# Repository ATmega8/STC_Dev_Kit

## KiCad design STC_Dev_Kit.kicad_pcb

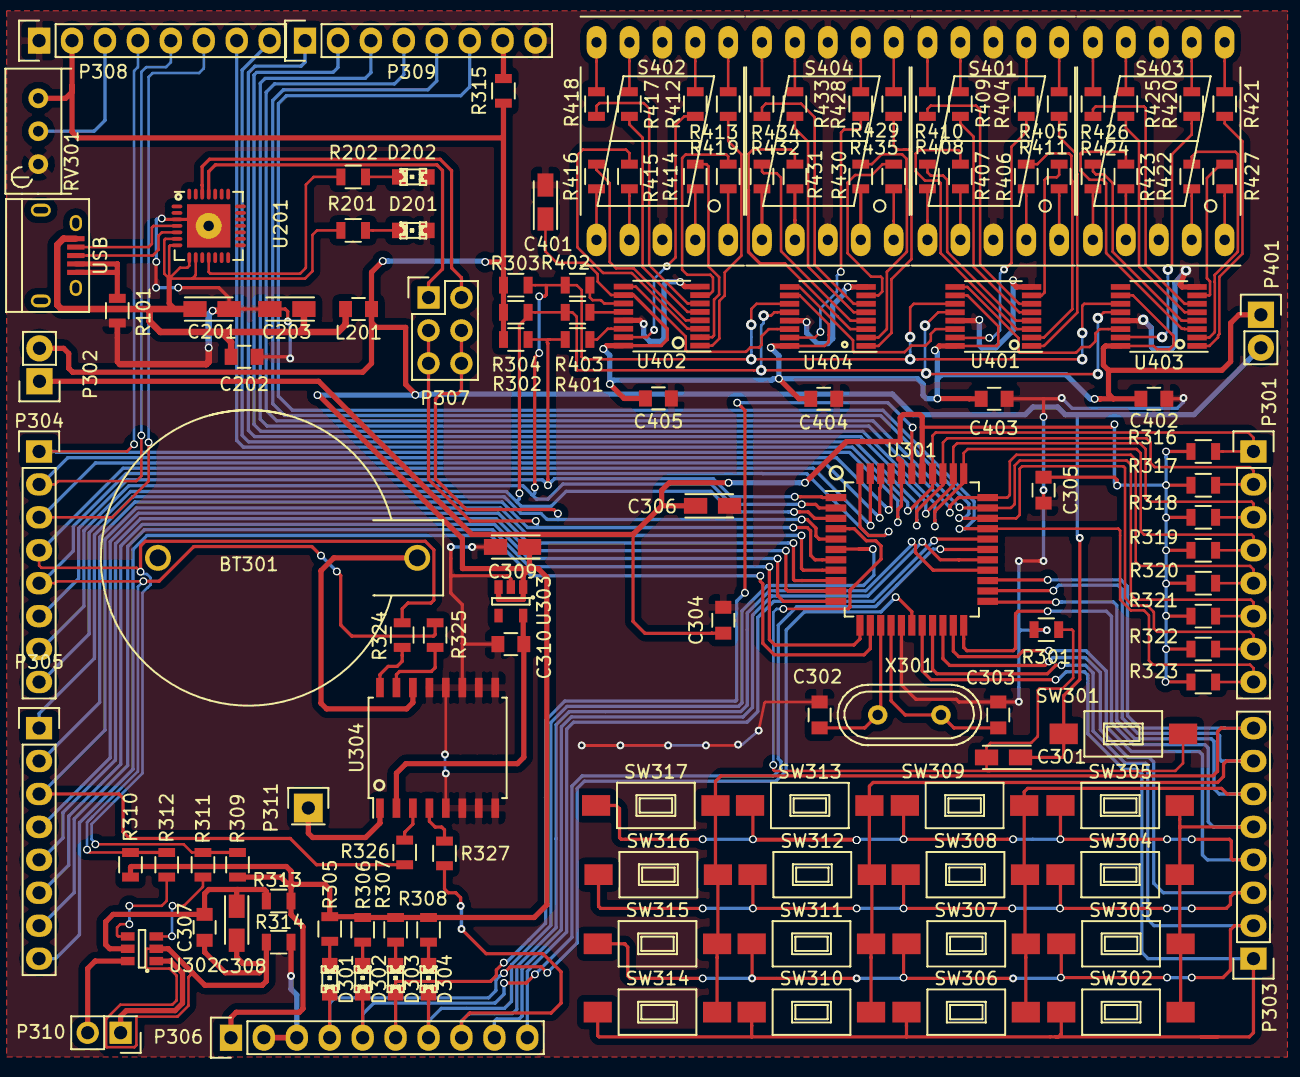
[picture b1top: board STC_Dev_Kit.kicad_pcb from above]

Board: 2 copper layers, 136 parts (0 on the bottom side), 144 nets.

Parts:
BT301: CR2032
C201: 4.7u; TantalC_SizeA_EIA-3216_Reflow
C202, C304, C305, C307, C310, C402, C403, C404, C405: 0.1u; C_0805
C203, C301, C306, C308, C309, C401: 10u; TantalC_SizeA_EIA-3216_Reflow
C302, C303: 22p; C_0805
D201: LED_PWR; LED-0805
D202: LED_STATUS; LED-0805
D301, D302, D303, D304: LED; LED-0805
L201: INDUCTOR_SMALL; C_0805
P301: P0; Pin_Header_Straight_1x08
P302: P1; Pin_Header_Straight_1x08
P303: P2; Pin_Header_Straight_1x08
P304: MCU POWER; Pin_Header_Straight_1x02
P305: P3; Pin_Header_Straight_1x08
P306: P4; Pin_Header_Straight_1x10
P307: USART SWITCH; Pin_Header_Straight_2x03
P308: LCD1602; Pin_Header_Straight_1x08
P309: CONN_8; Pin_Header_Straight_1x08
P310: Analog Input; Pin_Header_Straight_2x01
P311: 32KHz Out; Pin_Header_Straight_1x01
P401: LED POWER; Pin_Header_Straight_1x02
R101, R311, R312, R313, R314, R324, R325, R401, R402, R403: 0; R_0805
R201, R202, R302, R303, R304, R309, R310, R316, R317, R318, R319, R320, R321, R322, R323: 4.7k; R_0805
R301: 10k; R_0805
R305, R306, R307, R308, R326, R327: 1k; R_0805
R315: 10; R_0805
R404, R405, R406, R407, R408, R409, R410, R411, R412, R413, R414, R415, R416, R417, R418, R419, R420, R421, R422, R423, R424, R425, R426, R427, R428, R429, R430, R431, R432, R433, R434, R435: 470; R_0805
RV301: 10k; Potentiometer_Bourns_3296W_3-8Zoll_Inline_ScrewUp
S401, S402, S403, S404: 7SEGM; 7SegmentLED_LTS6760_LTS6780
SW301: RESET; SW_SPST_FSMSM
SW302, SW303, SW304, SW305, SW306, SW307, SW308, SW309, SW310, SW311, SW312, SW313, SW314, SW315, SW316, SW317: SW_PUSH_SMALL; SW_SPST_FSMSM
U201: CP2102; QFN-28-1EP_5x5mm_Pitch0.5mm
U301: STC89C52RC; LQFP-44_10x10mm_Pitch0.8mm
U302: MCP3421; SOT-23-6
U303: TPS76933; SOT-23-5
U304: DS3231; SOIC-16_7.5x10.3mm_Pitch1.27mm
U401, U402, U403, U404: 74HC595; TSSOP-16_4.4x5mm_Pitch0.65mm
USB: USB_CONN; USB_Micro-B
X301: CRYSTAL; Crystal_HC49-U_Vertical

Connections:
+5V: C301.1, C309.1, L201.2, P304.2, P306.1, P308.2, P401.2, R302.2, R303.2, R304.2, R305.1, R306.1, R307.1, R308.1, R309.2, R310.2, R313.2, R315.2, RV301.3, SW301.2, U303.1, U303.3
/LED_Display/DS: P302.6, R302.1, R401.2, U301.1
/LED_Display/DSO1: U402.9, U404.14
/LED_Display/DSO2: U401.14, U404.9
/LED_Display/DSO3: U401.9, U403.14
/STC_CORE/ADC_VDD: C307.1, C308.1, R313.1, U302.5
/STC_CORE/ADC_VSS: C307.2, C308.2, R314.1, U302.2
/STC_CORE/LED_RCK: P302.8, R304.1, R403.2, U301.3, U401.12, U403.12, U404.12
/STC_CORE/LED_SCK: P302.7, R303.1, R402.2, U301.2, U401.11, U403.11, U404.11
/STC_CORE/MCU_VDD: C304.1, C305.1, C306.1, P304.1, R316.1, R317.1, R318.1, R319.1, R320.1, R321.1, R322.1, R323.1, U301.38
/STC_CORE/P0.0: P301.1, P308.7, R316.2, U301.37
/STC_CORE/P0.1: P301.2, P308.8, R317.2, U301.36
/STC_CORE/P0.2: P301.3, P309.1, R318.2, U301.35
/STC_CORE/P0.3: P301.4, P309.2, R319.2, U301.34
/STC_CORE/P0.4: P301.5, P309.3, R320.2, U301.33
/STC_CORE/P0.5: P301.6, P309.4, R321.2, U301.32
/STC_CORE/P0.6: P301.7, P309.5, R322.2, U301.31
/STC_CORE/P0.7: P301.8, P309.6, R323.2, U301.30
/STC_CORE/P1.0: P302.1, P308.4, U301.40
/STC_CORE/P1.1: P302.2, P308.5, U301.41
/STC_CORE/P1.2: P302.3, P308.6, U301.42
/STC_CORE/P1.3: P302.4, R309.1, R311.2, R324.1, U301.43
/STC_CORE/P1.4: P302.5, R310.1, R312.2, R325.1, U301.44
/STC_CORE/P2.0: P303.1, SW302.1, SW306.1, SW310.1, SW314.1, U301.18
/STC_CORE/P2.1: P303.2, SW303.1, SW307.1, SW311.1, SW315.1, U301.19
/STC_CORE/P2.2: P303.3, SW304.1, SW308.1, SW312.1, SW316.1, U301.20
/STC_CORE/P2.3: P303.4, SW305.1, SW309.1, SW313.1, SW317.1, U301.21
/STC_CORE/P2.4: P303.5, SW302.2, SW303.2, SW304.2, SW305.2, U301.22
/STC_CORE/P2.5: P303.6, SW306.2, SW307.2, SW308.2, SW309.2, U301.23
/STC_CORE/P2.6: P303.7, SW310.2, SW311.2, SW312.2, SW313.2, U301.24
/STC_CORE/P2.7: P303.8, SW314.2, SW315.2, SW316.2, SW317.2, U301.25
/STC_CORE/P3.0: P305.1, P307.4, P307.6, U301.5
/STC_CORE/P3.1: P305.2, P307.3, P307.5, U301.7
/STC_CORE/P3.2: P305.3, R326.2, U301.8
/STC_CORE/P3.3: P305.4, U301.9
/STC_CORE/P3.4: P305.5, U301.10
/STC_CORE/P3.5: P305.6, U301.11
/STC_CORE/P3.6: P305.7, U301.12
/STC_CORE/P3.7: P305.8, U301.13
/STC_CORE/P4.0: D301.2, P306.4, U301.17
/STC_CORE/P4.1: D302.2, P306.5, U301.28
/STC_CORE/P4.2: D303.2, P306.6, U301.39
/STC_CORE/P4.3: D304.2, P306.7, U301.6
/STC_CORE/P4.4: P306.8, R327.2, U301.26
/STC_CORE/P4.5: P306.9, U301.27
/STC_CORE/P4.6: P306.10, U301.29
/STC_CORE/PC_RXD: P307.1, U201.25
/STC_CORE/PC_TXD: P307.2, U201.26
/USB2USART/SUSPEND: R202.2, U201.11
/USB2USART/USB_D+: U201.5, USB.3
/USB2USART/USB_D-: U201.4, USB.2
/USB2USART/VBUS: C201.1, C202.1, C203.1, L201.1, R201.2, U201.6, U201.7, U201.8, U201.9, USB.1
DGND: BT301.2, C201.2, C202.2, C203.2, C302.2, C303.2, C304.2, C305.2, C306.2, C309.2, C310.2, C401.2, C402.2, C403.2, C404.2, C405.2, D201.2, D202.2, P306.2, P306.3, P308.1, P309.8, R101.1, R301.2, R314.2, RV301.1, S401.3, S401.8, S402.3, S402.8, S403.3, S403.8, S404.3, S404.8, U201.3, U201.29, U301.16, U303.2, U304.5, U304.6, U304.7, U304.8, U304.9, U304.10, U304.11, U304.12, U304.13, U401.8, U401.13, U402.8, U402.13, U403.8, U403.13, U404.8, U404.13
unnamed: BT301.1, U304.14
unnamed: C301.2, R301.1, SW301.1, U301.4
unnamed: C302.1, U301.14, X301.1
unnamed: C303.1, U301.15, X301.2
unnamed: C310.1, U303.5, U304.2
unnamed: D201.1, R201.1
unnamed: D202.1, R202.1
unnamed: D301.1, R305.2
unnamed: D302.1, R306.2
unnamed: D303.1, R307.2
unnamed: D304.1, R308.2
unnamed: P308.3, RV301.2
unnamed: P309.7, R315.1
unnamed: P310.1, U302.1
unnamed: P310.2, U302.6
unnamed: P311.1, U304.1
unnamed: R101.2, USB.4, USB.5
unnamed: R311.1, U302.3
unnamed: R312.1, U302.4
unnamed: R324.2, U304.16
unnamed: R325.2, U304.15
unnamed: R326.1, U304.3
unnamed: R327.1, U304.4
unnamed: R401.1, U402.14
unnamed: R402.1, U402.11
unnamed: R403.1, U402.12
unnamed: R404.1, S401.7
unnamed: R404.2, U401.15
unnamed: R405.1, S401.6
unnamed: R405.2, U401.1
unnamed: R406.1, S401.4
unnamed: R406.2, U401.2
unnamed: R407.1, S401.2
unnamed: R407.2, U401.3
unnamed: R408.1, S401.1
unnamed: R408.2, U401.4
unnamed: R409.1, S401.9
unnamed: R409.2, U401.5
unnamed: R410.1, S401.10
unnamed: R410.2, U401.6
unnamed: R411.1, S401.5
unnamed: R411.2, U401.7
unnamed: R412.1, S402.7
unnamed: R412.2, U402.15
unnamed: R413.1, S402.6
unnamed: R413.2, U402.1
unnamed: R414.1, S402.4
unnamed: R414.2, U402.2
unnamed: R415.1, S402.2
unnamed: R415.2, U402.3
unnamed: R416.1, S402.1
unnamed: R416.2, U402.4
unnamed: R417.1, S402.9
unnamed: R417.2, U402.5
unnamed: R418.1, S402.10
unnamed: R418.2, U402.6
unnamed: R419.1, S402.5
unnamed: R419.2, U402.7
unnamed: R420.1, S403.7
unnamed: R420.2, U403.15
unnamed: R421.1, S403.6
unnamed: R421.2, U403.1
unnamed: R422.1, S403.4
unnamed: R422.2, U403.2
unnamed: R423.1, S403.2
unnamed: R423.2, U403.3
unnamed: R424.1, S403.1
unnamed: R424.2, U403.4
unnamed: R425.1, S403.9
unnamed: R425.2, U403.5
unnamed: R426.1, S403.10
unnamed: R426.2, U403.6
unnamed: R427.1, S403.5
unnamed: R427.2, U403.7
unnamed: R428.1, S404.7
unnamed: R428.2, U404.15
unnamed: R429.1, S404.6
unnamed: R429.2, U404.1
unnamed: R430.1, S404.4
unnamed: R430.2, U404.2
unnamed: R431.1, S404.2
unnamed: R431.2, U404.3
unnamed: R432.1, S404.1
unnamed: R432.2, U404.4
unnamed: R433.1, S404.9
unnamed: R433.2, U404.5
unnamed: R434.1, S404.10
unnamed: R434.2, U404.6
unnamed: R435.1, S404.5
unnamed: R435.2, U404.7
VCC: C401.1, C402.1, C403.1, C404.1, C405.1, P401.1, U401.10, U401.16, U402.10, U402.16, U403.10, U403.16, U404.10, U404.16

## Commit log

2015-09-20 frist commit
